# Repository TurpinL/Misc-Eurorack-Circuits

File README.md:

# Misc Eurorack Circuits
Some little circuits I've put together. Mostly heavily referencing if not directly copying other open source circuits. References to be added.

Warning: None of these have been heavily tested (or even lightly, really)

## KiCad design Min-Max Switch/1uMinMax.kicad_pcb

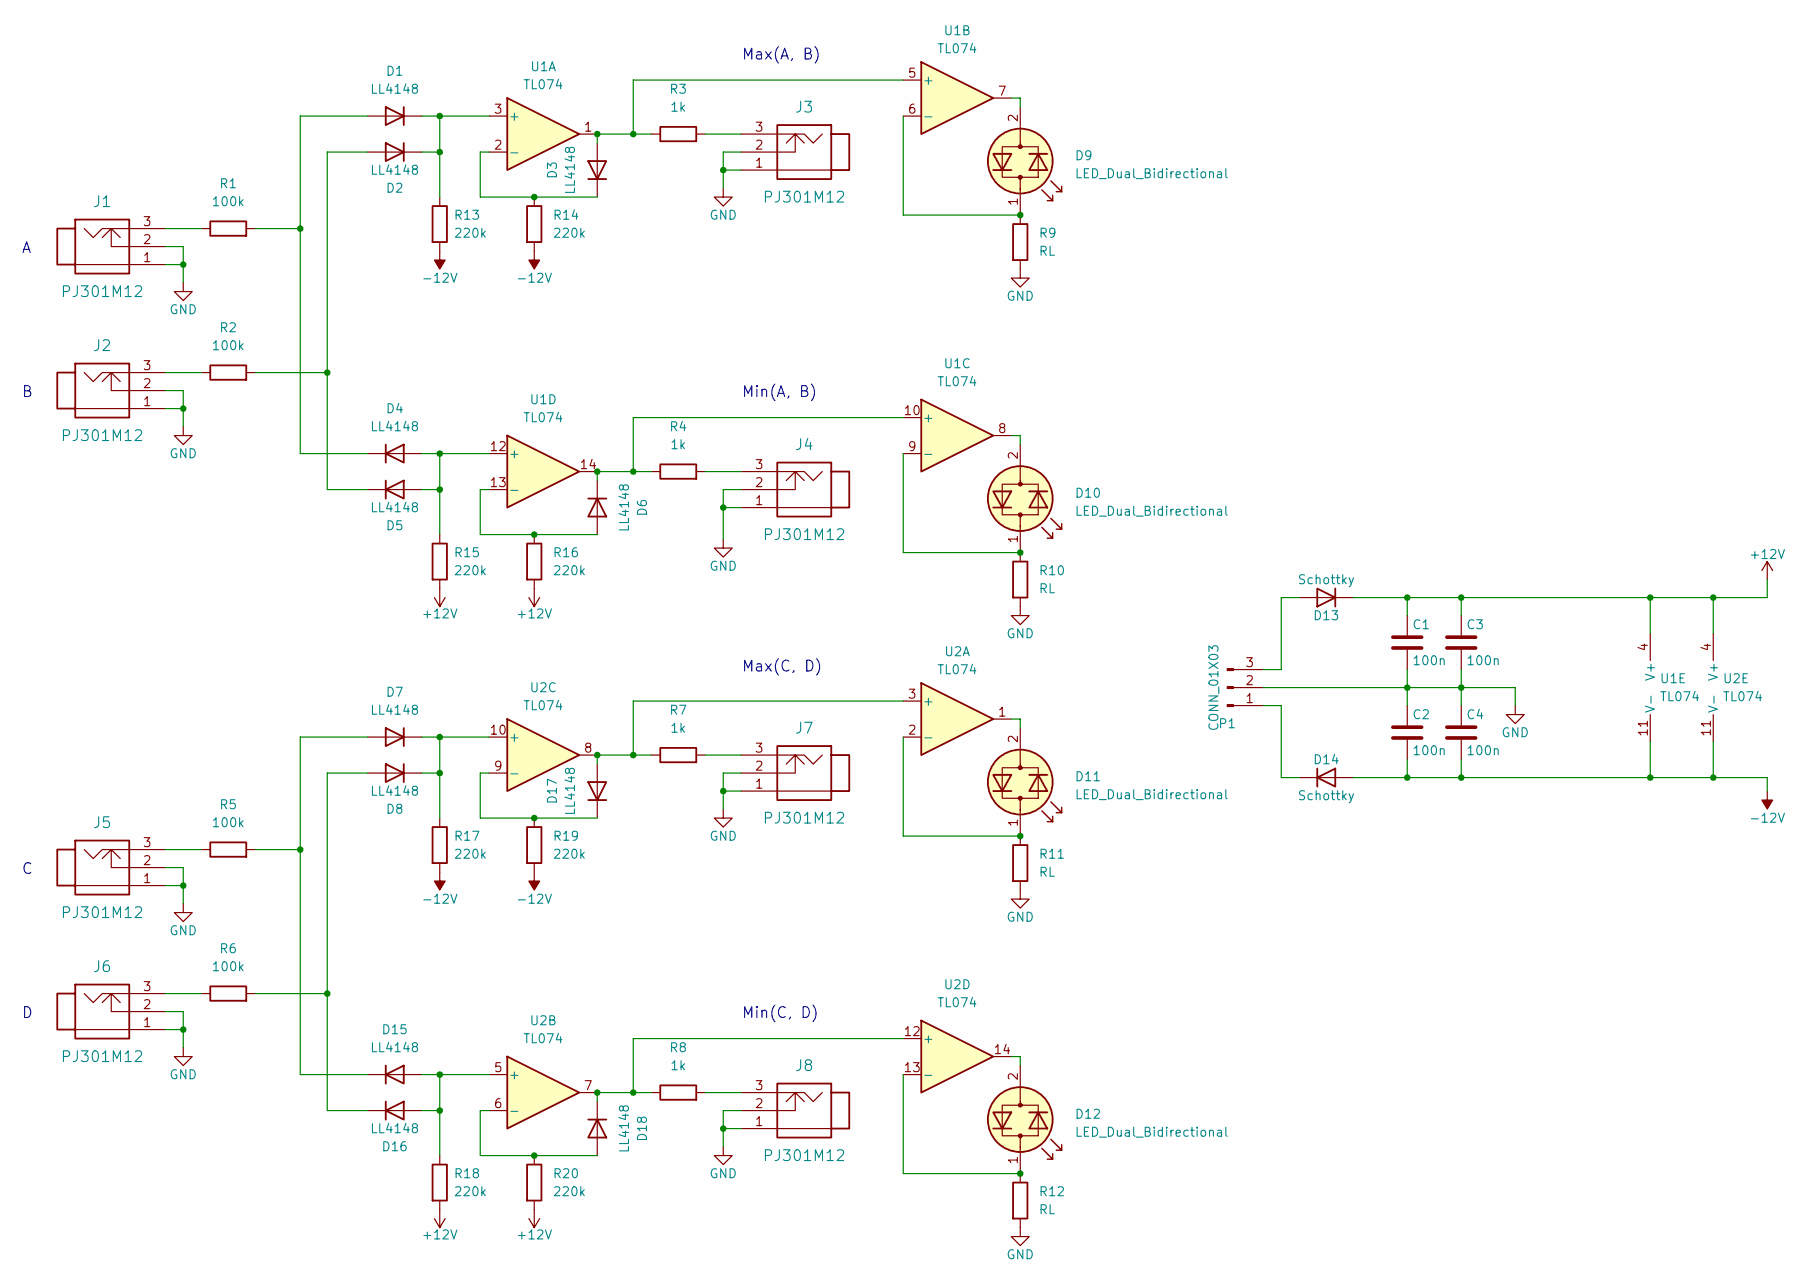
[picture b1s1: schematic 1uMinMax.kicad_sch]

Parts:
C1, C2, C3, C4: 100n; C_0805_2012Metric_Pad1.18x1.45mm_HandSolder
D1, D2, D3, D4, D5, D6, D7, D8, D15, D16, D17, D18: LL4148; D_SOD-323_HandSoldering
D9, D10, D11, D12: LED_Dual_Bidirectional; LED_D3.0mm_Clear
D13, D14: Schottky; D_SOD-323_HandSoldering
J1, J2, J3, J4, J5, J6, J7, J8: PJ301M12; Jack_3.5mm_QingPu_WQP-PJ398SM_Vertical_CircularHoles
P1: CONN_01X03; IDC-Header_2x05_P2.54mm_Vertical
R1, R2, R5, R6: 100k; R_0805_2012Metric_Pad1.20x1.40mm_HandSolder
R3, R4, R7, R8: 1k; R_0805_2012Metric_Pad1.20x1.40mm_HandSolder
R9, R10, R11, R12: RL; R_0805_2012Metric_Pad1.20x1.40mm_HandSolder
R13, R14, R15, R16, R17, R18, R19, R20: 220k; R_0805_2012Metric_Pad1.20x1.40mm_HandSolder
U1, U2: TL074; SOIC-14_3.9x8.7mm_P1.27mm

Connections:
+12V: C1.1, C3.1, D13.1 (K), R15.2, R16.2, R18.2, R20.2, U1.4 (V+), U2.4 (V+)
-12V: C2.2, C4.2, D14.2 (A), R13.2, R14.2, R17.2, R19.2, U1.11 (V-), U2.11 (V-)
GND: C1.2, C2.1, C3.2, C4.1, J1.1, J1.2, J2.1, J2.2, J3.1, J3.2, J4.1, J4.2, J5.1, J5.2, J6.1, J6.2, J7.1, J7.2, J8.1, J8.2, P1.2, R9.2, R10.2, R11.2, R12.2
unnamed: D1.2 (A), D4.1 (K), R1.2
unnamed: D1.1 (K), D2.1 (K), R13.1, U1.3 (+)
unnamed: D2.2 (A), D5.1 (K), R2.2
unnamed: D3.2 (A), R3.1, U1.1, U1.5 (+)
unnamed: D3.1 (K), R14.1, U1.2 (-)
unnamed: D4.2 (A), D5.2 (A), R15.1, U1.12 (+)
unnamed: D6.2 (A), R16.1, U1.13 (-)
unnamed: D6.1 (K), R4.1, U1.10 (+), U1.14
unnamed: D7.1 (K), D8.1 (K), R17.1, U2.10 (+)
unnamed: D9.2 (AK), U1.7
unnamed: D9.1 (KA), R9.1, U1.6 (-)
unnamed: D10.2 (AK), U1.8
unnamed: D10.1 (KA), R10.1, U1.9 (-)
unnamed: D11.2 (AK), U2.1
unnamed: D11.1 (KA), R11.1, U2.2 (-)
unnamed: D12.2 (AK), U2.14
unnamed: D12.1 (KA), R12.1, U2.13 (-)
unnamed: D13.2 (A), P1.3
unnamed: D14.1 (K), P1.1
unnamed: D15.2 (A), D16.2 (A), R18.1, U2.5 (+)
unnamed: D7.2 (A), D15.1 (K), R5.2
unnamed: D8.2 (A), D16.1 (K), R6.2
unnamed: D17.2 (A), R7.1, U2.3 (+), U2.8
unnamed: D17.1 (K), R19.1, U2.9 (-)
unnamed: D18.2 (A), R20.1, U2.6 (-)
unnamed: D18.1 (K), R8.1, U2.7, U2.12 (+)
unnamed: J1.3, R1.1
unnamed: J2.3, R2.1
unnamed: J3.3, R3.2
unnamed: J4.3, R4.2
unnamed: J5.3, R5.1
unnamed: J6.3, R6.1
unnamed: J7.3, R7.2
unnamed: J8.3, R8.2

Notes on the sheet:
Max(C, D)
Min(C, D)
Max(A, B)
Min(A, B)

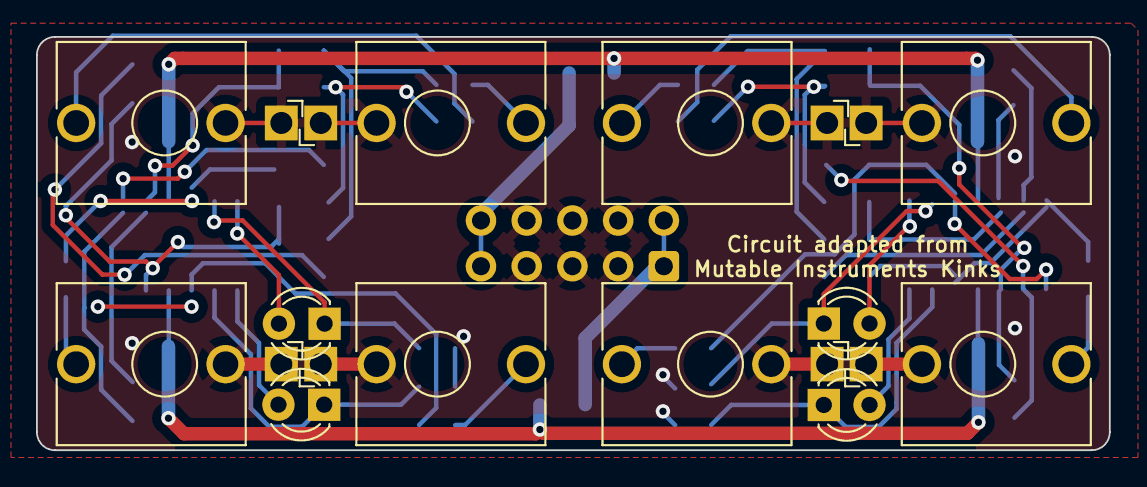
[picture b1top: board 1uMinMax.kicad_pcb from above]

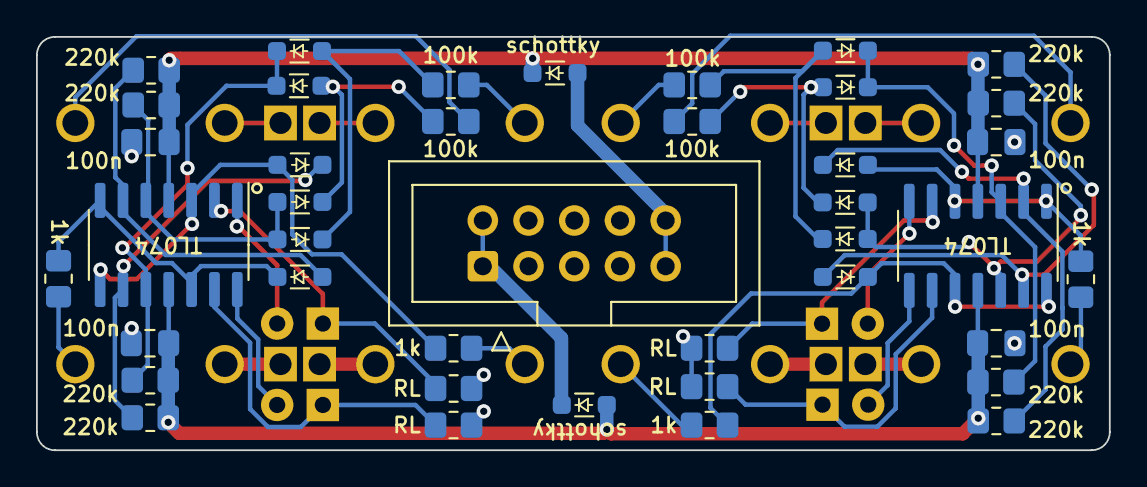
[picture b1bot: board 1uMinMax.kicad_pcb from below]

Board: 2 copper layers, 59.6 x 23.0 mm, 53 parts (41 on the bottom side), 37 nets.

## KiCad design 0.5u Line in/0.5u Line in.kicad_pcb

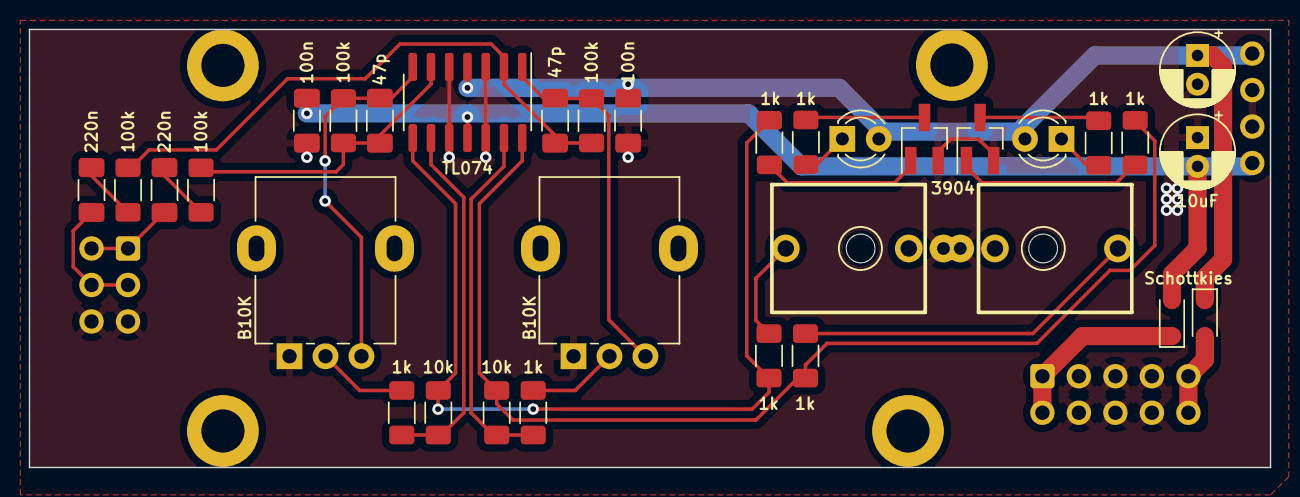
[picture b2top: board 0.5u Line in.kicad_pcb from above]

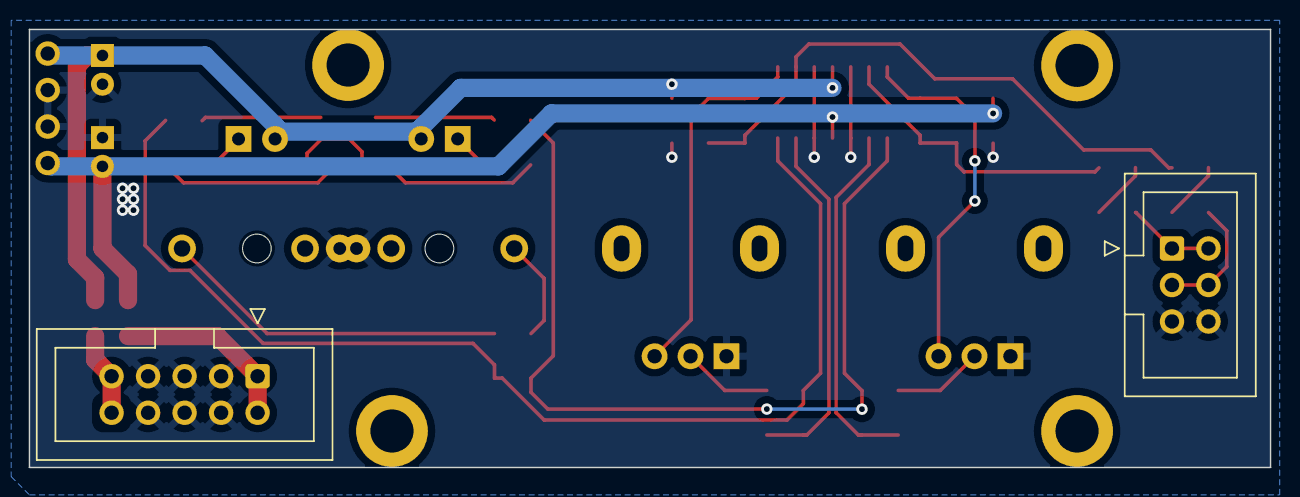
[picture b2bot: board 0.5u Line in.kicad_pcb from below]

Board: 2 copper layers, 86.4 x 30.5 mm, 36 parts (3 on the bottom side), 27 nets.

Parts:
C1, C2: 100n; C_1206_3216Metric_Pad1.33x1.80mm_HandSolder
C3, C4: 10uF; CP_Radial_D5.0mm_P2.00mm
C7, C9: 220n; C_1206_3216Metric_Pad1.33x1.80mm_HandSolder
C8, C10: 47p; C_1206_3216Metric_Pad1.33x1.80mm_HandSolder
D1, D2: D_Schottky; D_SOD-323_HandSoldering
D3, D4: LED; LED_D3.0mm_Clear
J1: Eurorack_Power_10pin_Unshrouded; IDC-Header_2x05_P2.54mm_Vertical
J2: Conn_01x04_Pin; PinHeader_1x04_P2.54mm_Vertical_no_silkscreen
J3: Conn_02x03; IDC-Header_2x03_P2.54mm_Vertical
J4, J5: IN R; EighthInch_PJ398SM_with_hole
Q1, Q2: 3904; SOT-23_Handsoldering
R1, R2, R8, R9: 100k; R_1206_3216Metric_Pad1.30x1.75mm_HandSolder
R3, R5, R6, R7, R10, R12, R13, R14: 1k; R_1206_3216Metric_Pad1.30x1.75mm_HandSolder
R4, R11: 10k; R_1206_3216Metric_Pad1.30x1.75mm_HandSolder
RV1, RV2: B10K; Potentiometer_Alpha_RD901F-40-00D_Single_Vertical
U1: TL074; SOIC-14_3.9x8.7mm_P1.27mm

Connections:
+12v: C1.2, C3.1, D1.1 (K), D3.2 (A), D4.2 (A), J2.1, U1.4 (V+)
-12v: C2.1, C4.2, D2.2 (A), J2.4, U1.11 (V-)
GND: C1.1, C2.2, C3.2, C4.1, J1.3 (GND), J1.4 (GND), J1.5 (GND), J1.6 (GND), J1.7 (GND), J1.8 (GND), J2.2, J2.3, J3.5 (GND), J3.6 (GND), J4.2 (SHEILD), J5.2 (SHEILD), Q1.2 (E), Q2.2 (E), RV1.1, RV2.1, U1.3 (+), U1.5 (+), U1.10 (+), U1.12 (+)
unnamed: C7.1, J3.1 (+12V), J3.2 (+12V)
unnamed: C7.2, R1.1
unnamed: C8.2, R2.2, RV1.3, U1.7
unnamed: C9.1, J3.3 (GND), J3.4 (GND)
unnamed: C9.2, R8.1
unnamed: C10.2, R9.2, RV2.3, U1.1
unnamed: D1.2 (A), J1.1 (+12V), J1.2 (+12V)
unnamed: D2.1 (K), J1.9 (-12V), J1.10 (-12V)
unnamed: D3.1 (K), R7.1
unnamed: D4.1 (K), R14.1
unnamed: J4.1 (SIG), R5.2
unnamed: J5.1 (SIG), R12.2
unnamed: Q1.1 (B), R6.2
unnamed: Q1.3 (C), R7.2
unnamed: Q2.1 (B), R13.2
unnamed: Q2.3 (C), R14.2
unnamed: R3.1, RV1.2
unnamed: R10.1, RV2.2
unnamed: C10.1, R8.2, R9.1, U1.2 (-)
unnamed: C8.1, R1.2, R2.1, U1.6 (-)
unnamed: R3.2, R4.1, U1.9 (-)
unnamed: R10.2, R11.1, U1.13 (-)
Out L: R4.2, R5.1, R6.1, U1.8
Out R: R11.2, R12.1, R13.1, U1.14

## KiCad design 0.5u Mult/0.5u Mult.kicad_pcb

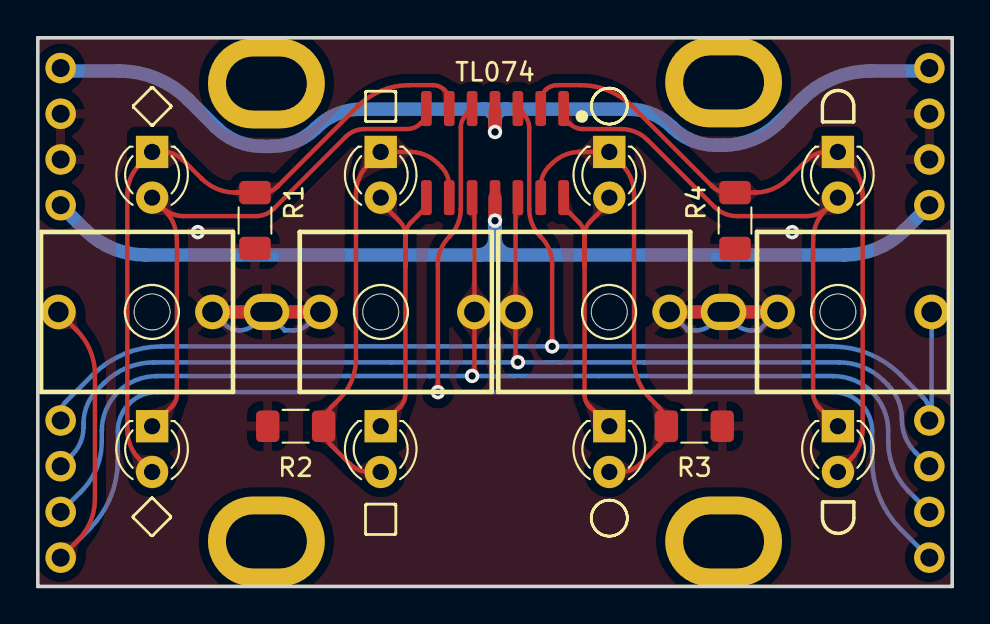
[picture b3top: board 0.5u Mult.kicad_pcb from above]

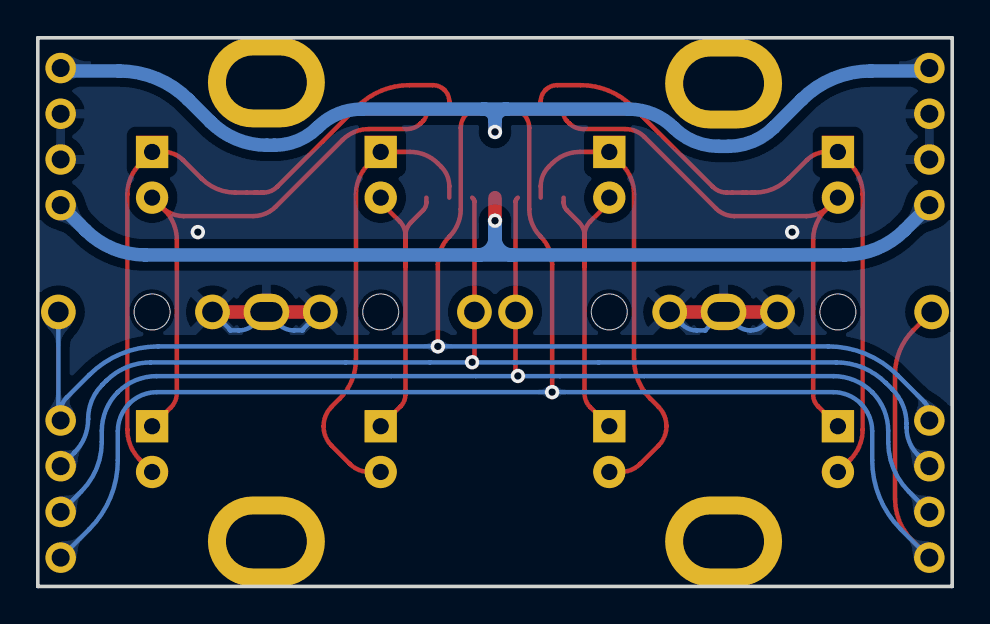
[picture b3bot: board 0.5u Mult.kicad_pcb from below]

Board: 2 copper layers, 50.8 x 30.5 mm, 21 parts (4 on the bottom side), 15 nets.

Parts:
D1, D2, D3, D4, D5, D6, D7, D8: LED; LED_D3.0mm
J1, J2, J3, J4: 3.5mm_Mono_Switched; EighthInch_PJ398SM_with_hole
J5, J6, J7, J8: Conn_01x04_Pin; PinHeader_1x04_P2.54mm_Vertical_no_silkscreen
R1, R2, R3, R4: 1k; R_1206_3216Metric_Pad1.30x1.75mm_HandSolder
TL074: TL074; SOIC-14_3.9x8.7mm_P1.27mm

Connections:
+12v: J5.1, J8.1, TL074.4 (V+)
-12v: J5.4, J8.4, TL074.11 (V-)
GND: J1.2 (SHEILD), J1.3 (SW), J2.3 (SW), J3.2 (SHEILD), J3.3 (SW), J4.3 (SW), J5.2, J5.3, J8.2, J8.3, R1.2, R2.2, R3.2, R4.2
unnamed: D1.2 (A), D2.1 (K), TL074.7
unnamed: D1.1 (K), D2.2 (A), R1.1, TL074.6 (-)
unnamed: D3.2 (A), D4.1 (K), TL074.8
unnamed: D3.1 (K), D4.2 (A), R2.1, TL074.9 (-)
unnamed: D5.2 (A), D6.1 (K), TL074.14
unnamed: D5.1 (K), D6.2 (A), R3.1, TL074.13 (-)
unnamed: D7.2 (A), D8.1 (K), TL074.1
unnamed: D7.1 (K), D8.2 (A), R4.1, TL074.2 (-)
Signal 1: J1.1 (SIG), J6.1, J7.1, TL074.5 (+)
Signal 2: J2.1 (SIG), J6.2, J7.2, TL074.10 (+)
Signal 3: J3.1 (SIG), J6.3, J7.3, TL074.12 (+)
Signal 4: J4.1 (SIG), J6.4, J7.4, TL074.3 (+)

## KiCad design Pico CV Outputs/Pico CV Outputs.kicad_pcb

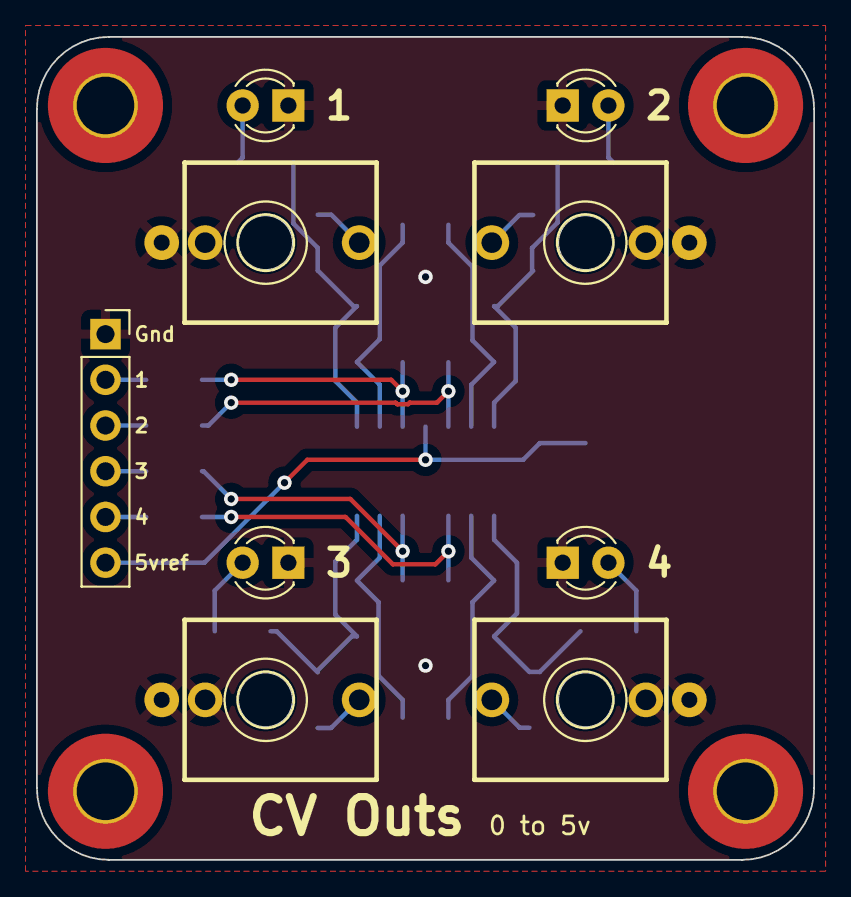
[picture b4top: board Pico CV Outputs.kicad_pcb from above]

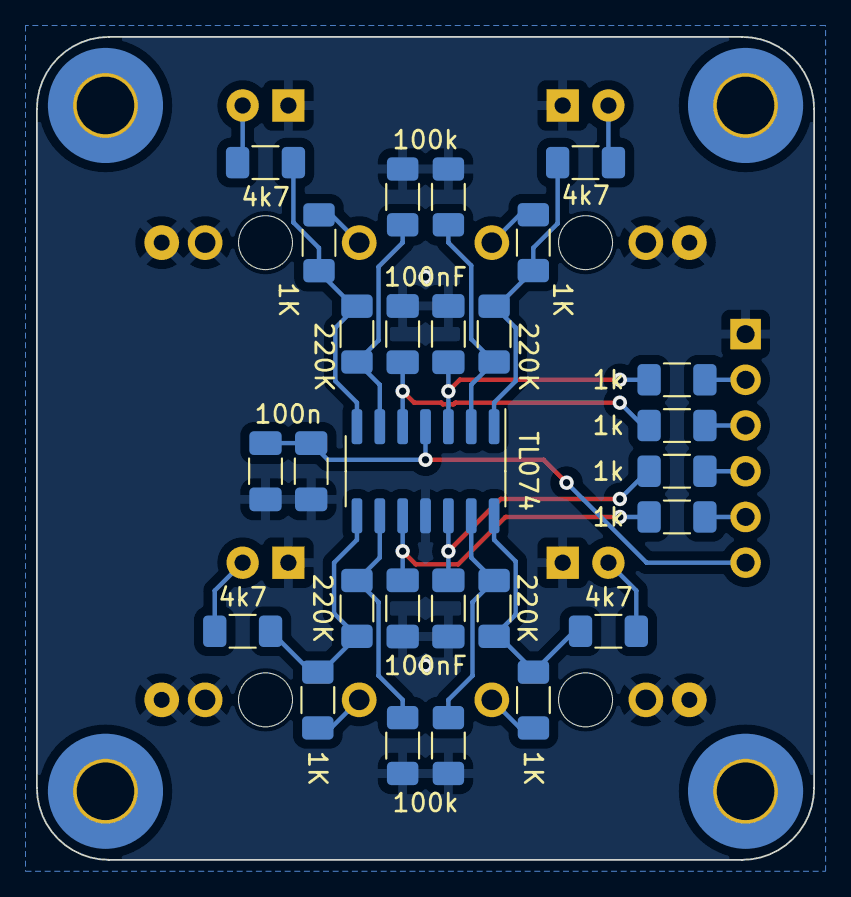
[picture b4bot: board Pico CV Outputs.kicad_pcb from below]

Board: 2 copper layers, 43.2 x 45.7 mm, 36 parts (27 on the bottom side), 26 nets.

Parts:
C1, C4, C5, C6: 100nF; C_1206_3216Metric_Pad1.33x1.80mm_HandSolder
C2, C3: 100n; C_1206_3216Metric_Pad1.33x1.80mm_HandSolder
D1, D2, D3, D4: LED; LED_D3.0mm
J1, J3, J4, J5: 3.5mm_Mono_Switched_SymSmall_0.05; EighthInch_PJ398SM_with_hole
J2: Conn_01x06_Socket; PinSocket_1x06_P2.54mm_Vertical
R1, R6, R11, R16: 1k; R_1206_3216Metric_Pad1.30x1.75mm_HandSolder
R2, R7, R12, R17: 100k; R_1206_3216Metric_Pad1.30x1.75mm_HandSolder
R3, R8, R13, R18: 220K; R_1206_3216Metric_Pad1.30x1.75mm_HandSolder
R4, R10, R15, R20: 1K; R_1206_3216Metric_Pad1.30x1.75mm_HandSolder
R5, R9, R14, R19: 4k7; R_1206_3216Metric_Pad1.30x1.75mm_HandSolder
U1: TL074; SOIC-14_3.9x8.7mm_P1.27mm

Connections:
5vref: C2.1, C3.1, J2.6, U1.4 (V+)
CV 1: J2.2, R1.1
CV 2: J2.3, R6.1
CV 3: J2.4, R11.1
CV 4: J2.5, R16.1
GND: C1.2, C2.2, C3.2, C4.2, C5.2, C6.2, D1.1 (K), D2.1 (K), D3.1 (K), D4.1 (K), J1.2 (SHEILD), J1.3 (SW), J2.1, J3.2 (SHEILD), J3.3 (SW), J4.2 (SHEILD), J4.3 (SW), J5.2 (SHEILD), J5.3 (SW), R2.1, R7.1, R12.1, R17.1, U1.11 (V-)
unnamed: D1.2 (A), R5.2
unnamed: D2.2 (A), R9.2
unnamed: D3.2 (A), R14.2
unnamed: D4.2 (A), R19.2
unnamed: J1.1 (SIG), R4.1
unnamed: J3.1 (SIG), R10.1
unnamed: J4.1 (SIG), R15.1
unnamed: J5.1 (SIG), R20.1
unnamed: R3.1, R4.2, R5.1, U1.1
unnamed: R8.1, R9.1, R10.2, U1.7
unnamed: R13.1, R14.1, R15.2, U1.14
unnamed: R18.1, R19.1, R20.2, U1.8
unnamed: C1.1, R1.2, U1.3 (+)
unnamed: R2.2, R3.2, U1.2 (-)
unnamed: C4.1, R6.2, U1.5 (+)
unnamed: R7.2, R8.2, U1.6 (-)
unnamed: C6.1, R16.2, U1.10 (+)
unnamed: R17.2, R18.2, U1.9 (-)
unnamed: C5.1, R11.2, U1.12 (+)
unnamed: R12.2, R13.2, U1.13 (-)

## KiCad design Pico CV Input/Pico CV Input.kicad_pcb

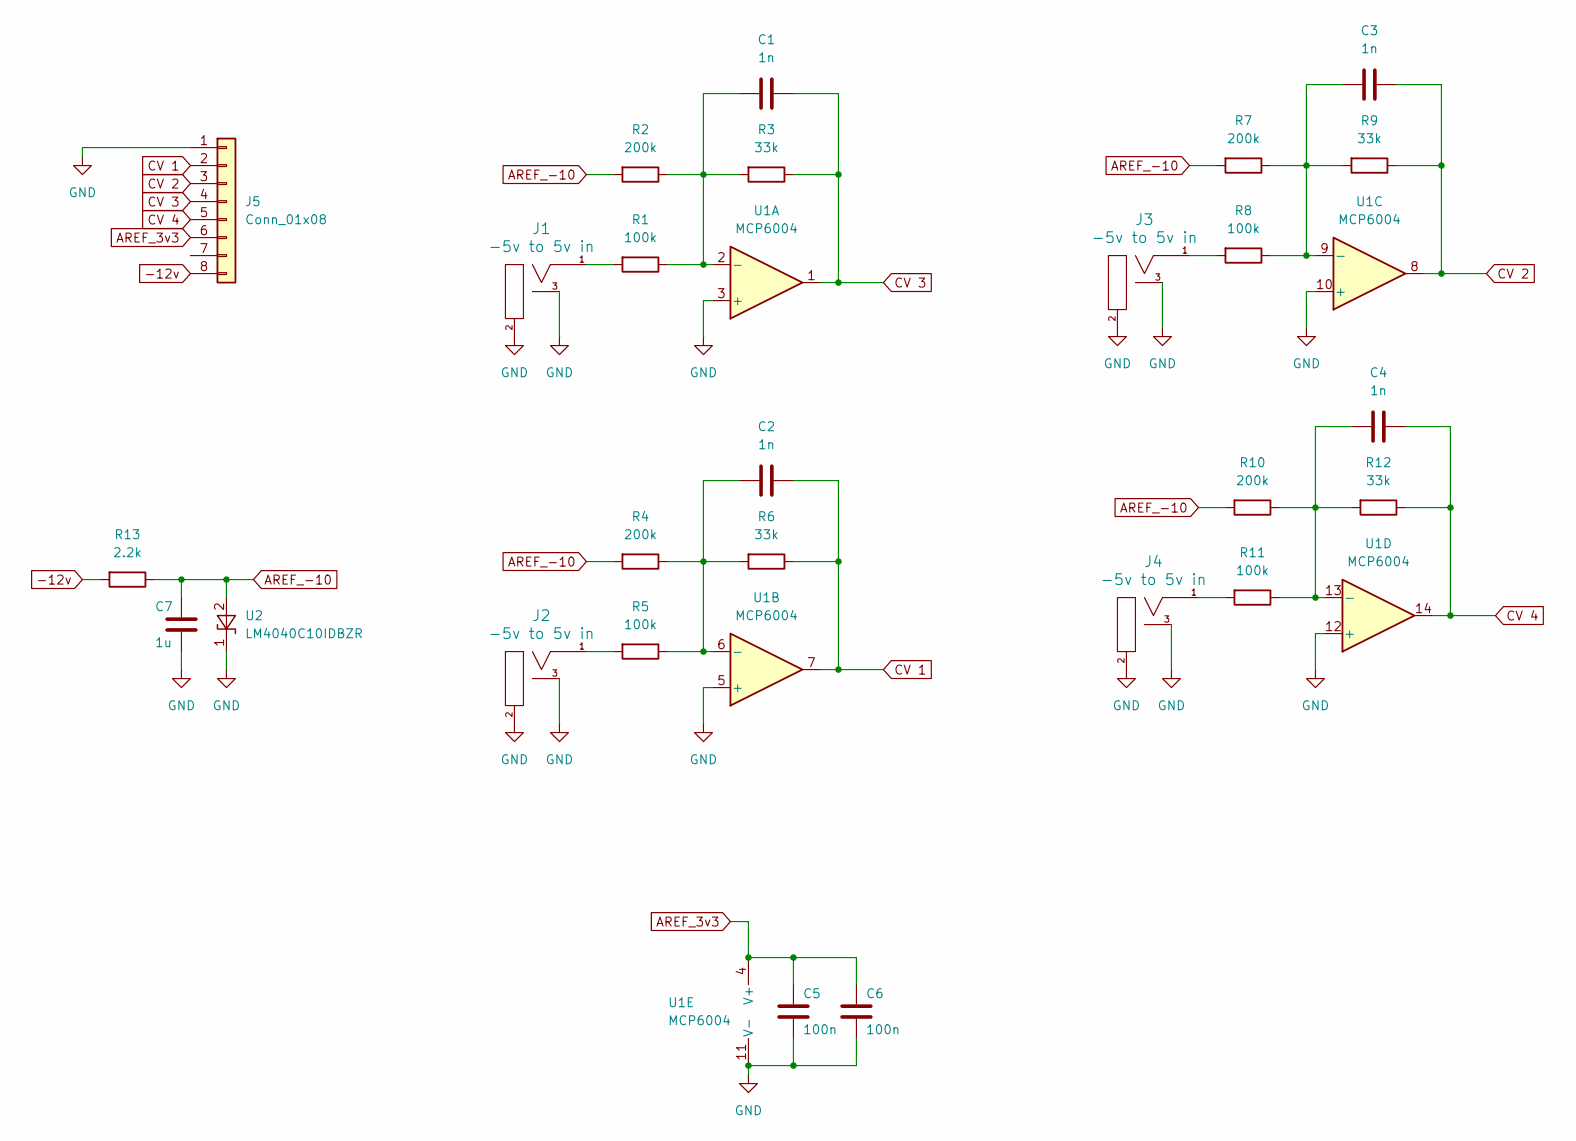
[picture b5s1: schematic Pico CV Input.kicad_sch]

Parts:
C1, C2, C3, C4: 1n; C_1206_3216Metric_Pad1.33x1.80mm_HandSolder
C5, C6: 100n; C_1206_3216Metric_Pad1.33x1.80mm_HandSolder
C7: 1u; C_1206_3216Metric_Pad1.33x1.80mm_HandSolder
J1, J2, J3, J4: -5v to 5v in; EighthInch_PJ398SM_with_hole; Part Number WQP-WQP518MA
J5: Conn_01x08; PinSocket_1x08_P2.54mm_Vertical
R1, R5, R8, R11: 100k; R_1206_3216Metric_Pad1.30x1.75mm_HandSolder
R2, R4, R7, R10: 200k; R_1206_3216Metric_Pad1.30x1.75mm_HandSolder
R3, R6, R9, R12: 33k; R_1206_3216Metric_Pad1.30x1.75mm_HandSolder
R13: 2.2k; R_1206_3216Metric_Pad1.30x1.75mm_HandSolder
U1: MCP6004; SOIC-14_3.9x8.7mm_P1.27mm
U2: LM4040C10IDBZR; SOT-23-3

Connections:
-12v: J5.8, R13.2
AREF_3v3: C5.1, C6.1, J5.6, U1.4 (V+)
AREF_-10: C7.1, R2.2, R4.2, R7.2, R10.2, R13.1, U2.2 (A)
CV 1: C2.2, J5.2, R6.1, U1.7
CV 2: C3.2, J5.3, R9.1, U1.8
CV 3: C1.2, J5.4, R3.1, U1.1
CV 4: C4.2, J5.5, R12.1, U1.14
GND: C5.2, C6.2, C7.2, J1.2 (SHEILD), J1.3 (SW), J2.2 (SHEILD), J2.3 (SW), J3.2 (SHEILD), J3.3 (SW), J4.2 (SHEILD), J4.3 (SW), J5.1, U1.3 (+), U1.5 (+), U1.10 (+), U1.11 (V-), U1.12 (+), U2.1 (K)
unnamed: J1.1 (SIG), R1.2
unnamed: J2.1 (SIG), R5.2
unnamed: J3.1 (SIG), R8.2
unnamed: J4.1 (SIG), R11.2
unnamed: C1.1, R1.1, R2.1, R3.2, U1.2 (-)
unnamed: C2.1, R4.1, R5.1, R6.2, U1.6 (-)
unnamed: C3.1, R7.1, R8.1, R9.2, U1.9 (-)
unnamed: C4.1, R10.1, R11.1, R12.2, U1.13 (-)

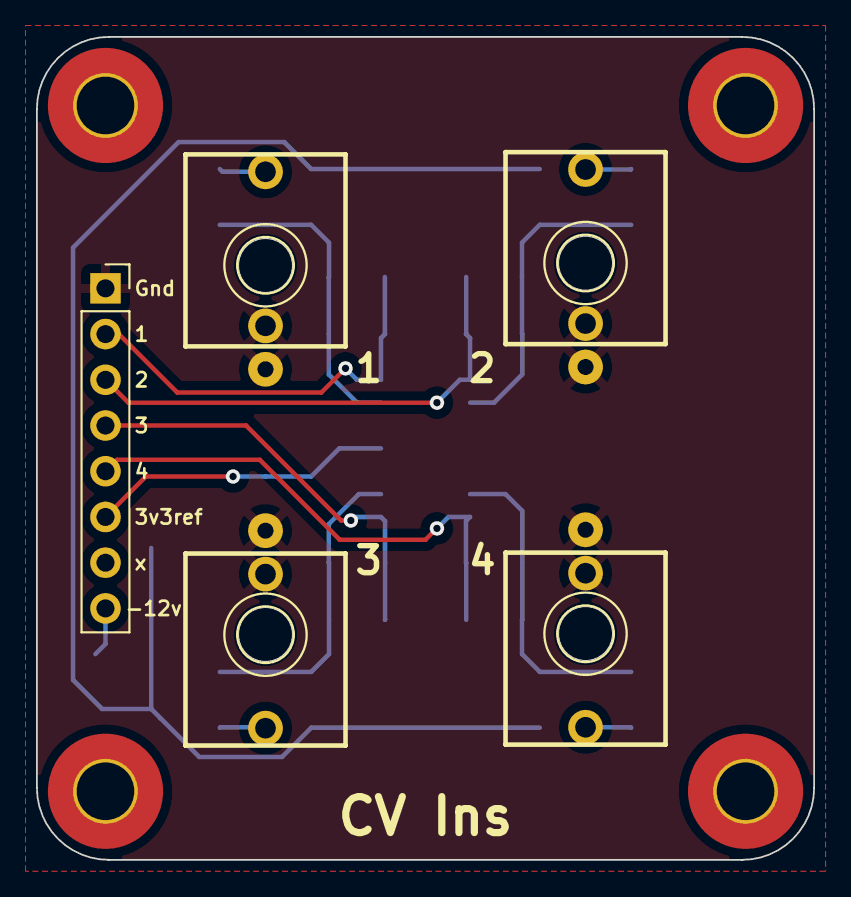
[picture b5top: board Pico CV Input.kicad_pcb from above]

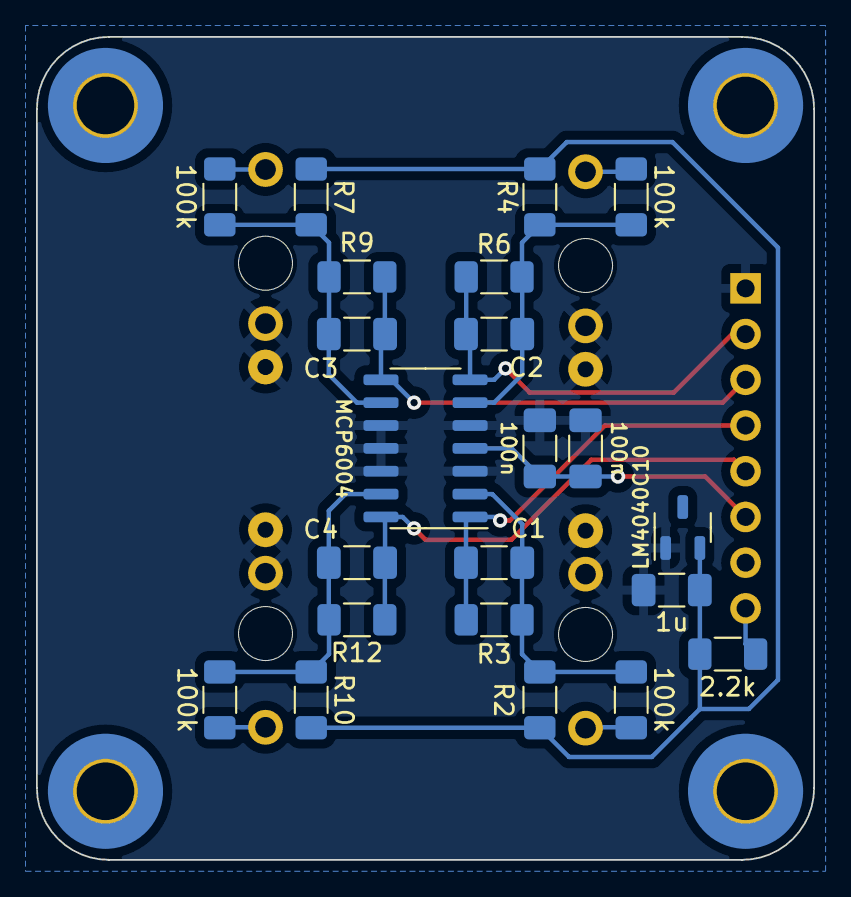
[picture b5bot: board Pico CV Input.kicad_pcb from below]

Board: 2 copper layers, 43.2 x 45.7 mm, 27 parts (22 on the bottom side), 16 nets.

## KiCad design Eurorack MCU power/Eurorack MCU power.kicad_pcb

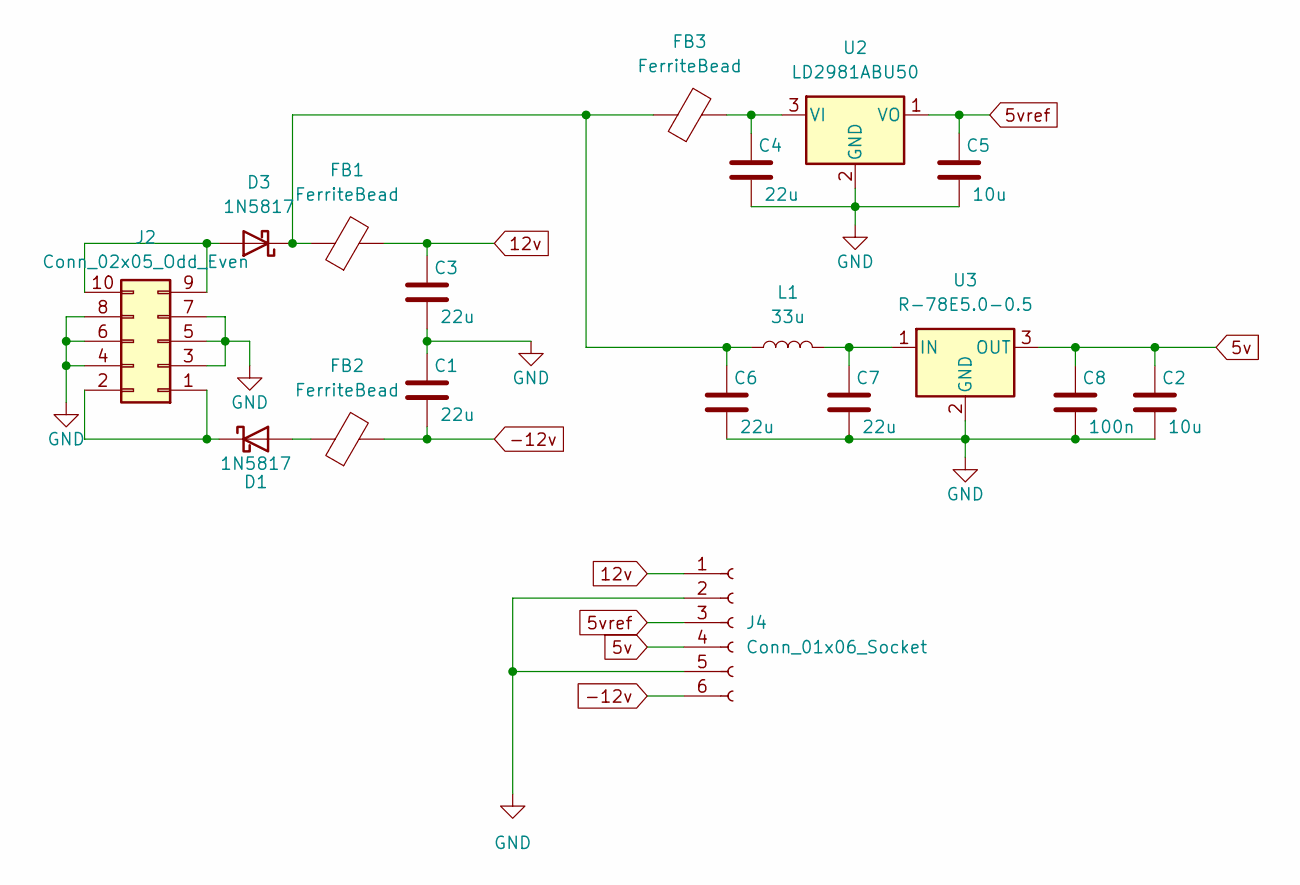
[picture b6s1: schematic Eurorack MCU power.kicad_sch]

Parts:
C1, C3, C4, C6, C7: 22u; C_1206_3216Metric_Pad1.33x1.80mm_HandSolder
C2, C5: 10u; C_1206_3216Metric_Pad1.33x1.80mm_HandSolder
C8: 100n; C_1206_3216Metric_Pad1.33x1.80mm_HandSolder
D1, D3: 1N5817; D_SOD-323_HandSoldering
FB1, FB2, FB3: FerriteBead; L_1206_3216Metric_Pad1.42x1.75mm_HandSolder
J2: Conn_02x05_Odd_Even; IDC-Header_2x05_P2.54mm_Vertical
J4: Conn_01x06_Socket; PinSocket_1x06_P2.54mm_Vertical
L1: 33u; L_0805_2012Metric_Pad1.15x1.40mm_HandSolder
U2: LD2981ABU50; SOT-89-3
U3: R-78E5.0-0.5; Converter_DCDC_RECOM_R-78E-0.5_THT

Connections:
5v: C2.2, C8.2, J4.4, U3.3 (OUT)
5vref: C5.2, J4.3, U2.1 (VO)
12v: C3.2, FB1.2, J4.1
-12v: C1.1, FB2.2, J4.6
GND: C1.2, C2.1, C3.1, C4.1, C5.1, C6.1, C7.1, C8.1, J2.3, J2.4, J2.5, J2.6, J2.7, J2.8, J4.2, J4.5, U2.2 (GND), U3.2 (GND)
unnamed: D1.2 (A), FB2.1
unnamed: D1.1 (K), J2.1, J2.2
unnamed: D3.2 (A), J2.9, J2.10
unnamed: C6.2, D3.1 (K), FB1.1, FB3.1, L1.1
unnamed: C4.2, FB3.2, U2.3 (VI)
unnamed: C7.2, L1.2, U3.1 (IN)

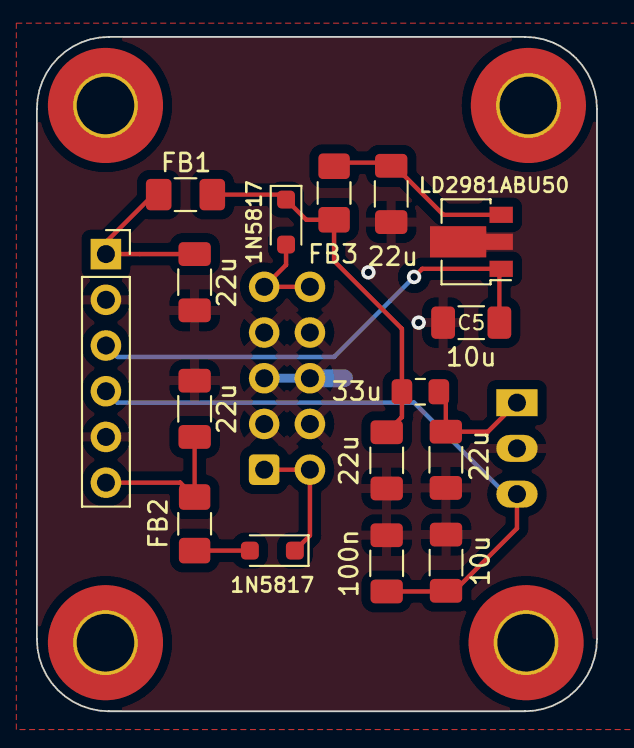
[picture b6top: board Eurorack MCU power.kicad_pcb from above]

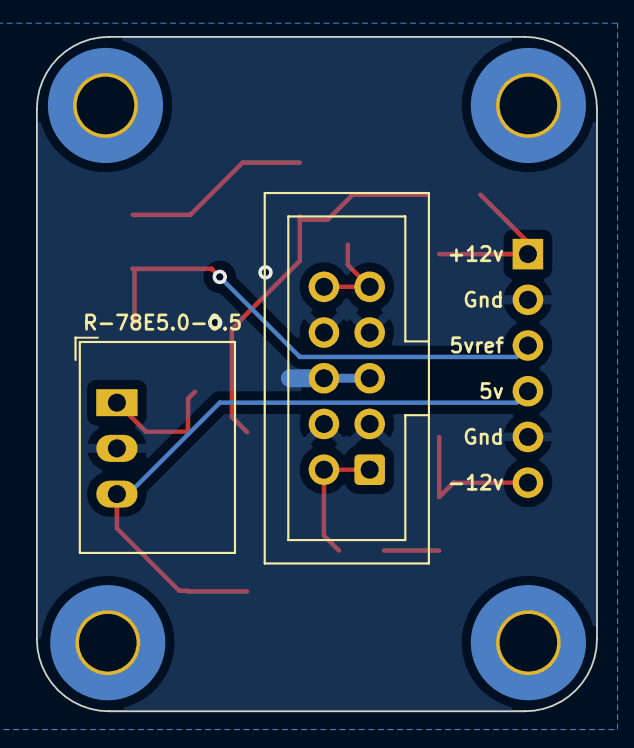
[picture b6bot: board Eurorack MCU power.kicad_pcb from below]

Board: 2 copper layers, 31.1 x 37.5 mm, 18 parts (2 on the bottom side), 11 nets.

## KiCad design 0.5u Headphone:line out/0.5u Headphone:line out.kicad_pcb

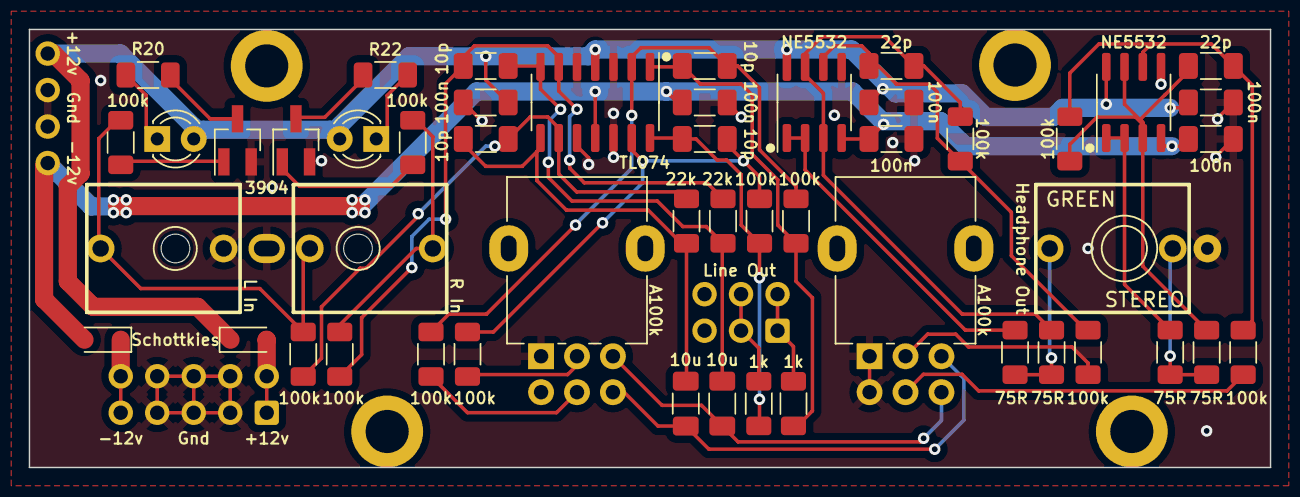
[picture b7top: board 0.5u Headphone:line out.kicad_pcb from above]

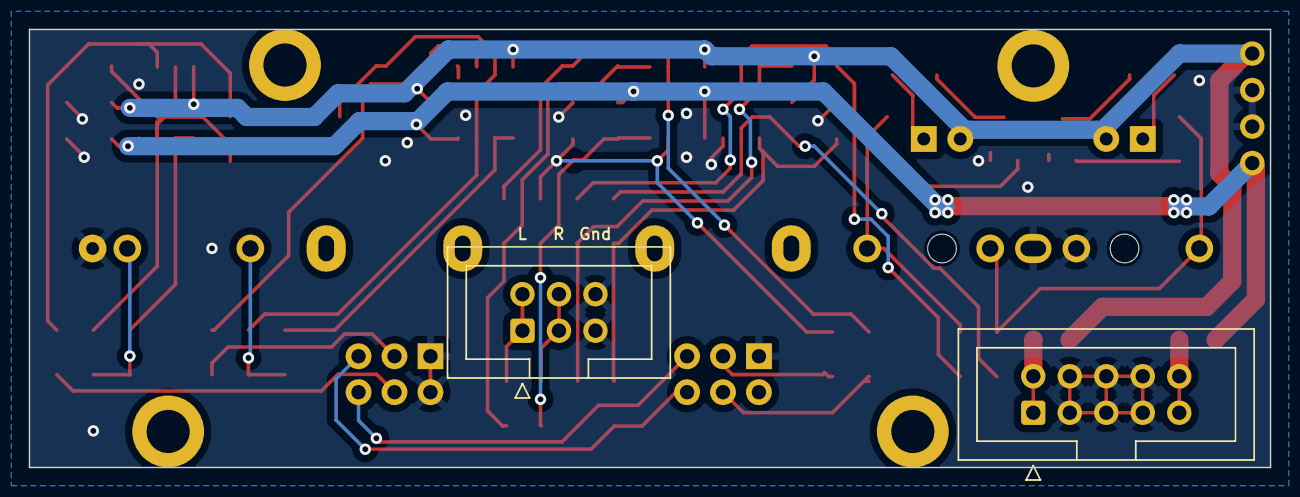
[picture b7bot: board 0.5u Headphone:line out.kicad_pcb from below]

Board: 2 copper layers, 86.4 x 30.5 mm, 53 parts (3 on the bottom side), 37 nets.

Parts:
C1, C2, C3, C4: 10p; C_1206_3216Metric_Pad1.33x1.80mm_HandSolder
C5, C6: 22p; C_1206_3216Metric_Pad1.33x1.80mm_HandSolder
C9, C10, C11, C12, C13, C14: 100n; C_1206_3216Metric_Pad1.33x1.80mm_HandSolder
C15, C16: 10u; C_1206_3216Metric_Pad1.33x1.80mm_HandSolder
D1, D2: LED; LED_D3.0mm_Clear
D3, D4: D_Schottky; D_SOD-323_HandSoldering
J1: IN L; EighthInch_PJ398SM_with_hole
J2: IN R; EighthInch_PJ398SM_with_hole
J3: Eurorack_Power_10pin_Unshrouded; IDC-Header_2x05_P2.54mm_Vertical
J4: 3.5mm_Stereo; EighthInch_Stereo_PJ366ST
J5: Conn_02x03; IDC-Header_2x03_P2.54mm_Vertical
J6: Conn_01x04_Pin; PinHeader_1x04_P2.54mm_Vertical_no_silkscreen
Q1, Q2: 3904; SOT-23_Handsoldering
R1, R3, R4, R6, R8, R9, R11, R12, R14, R15, R19, R21: 100k; R_1206_3216Metric_Pad1.30x1.75mm_HandSolder
R2, R7: 22k; R_1206_3216Metric_Pad1.30x1.75mm_HandSolder
R5, R10, R20, R22: 1k; R_1206_3216Metric_Pad1.30x1.75mm_HandSolder
R13, R16, R23, R24: 75R; R_1206_3216Metric_Pad1.30x1.75mm_HandSolder
RV1, RV2: R_Potentiometer_Dual 100k; Potentiometer_Alpha_RD902F-40-00D_Dual_Vertical
U1: TL074; SOIC-14_3.9x8.7mm_P1.27mm
U3, U4: NE5532; SOIC-8_3.9x4.9mm_P1.27mm

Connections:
+12v: C9.2, C11.2, C13.2, D1.2 (A), D2.2 (A), D3.1 (K), J6.1, U1.4 (V+), U3.8 (V+), U4.8 (V+)
-12v: C10.1, C12.1, C14.1, D4.2 (A), J6.4, U1.11 (V-), U3.4 (V-), U4.4 (V-)
GND: C9.1, C10.2, C11.1, C12.2, C13.1, C14.2, J1.2 (SHEILD), J1.3 (SW), J3.3 (GND), J3.4 (GND), J3.5 (GND), J3.6 (GND), J3.7 (GND), J3.8 (GND), J4.2 (SHEILD), J5.5 (GND), J5.6 (GND), J6.2, J6.3, Q1.2 (E), Q2.2 (E), RV1.1, RV1.4, RV2.1, U1.3 (+), U1.5 (+), U1.10 (+), U1.12 (+), U3.5 (+), U4.5 (+)
In L: J1.1 (SIG), J2.3 (SW), R1.1, R19.1
In R: J2.1 (SIG), R6.1, R21.1
Intermediate L: C15.2, RV1.3, RV2.6
Intermediate R: C16.2, RV1.6, RV2.3
unnamed: C1.2, C15.1, R2.2, U1.8
unnamed: C2.2, R4.2, R5.1, U1.1
unnamed: C4.2, R9.2, R10.1, U1.14
unnamed: C3.2, C16.1, R7.2, U1.7
unnamed: D1.1 (K), R20.1
unnamed: D2.1 (K), R22.1
unnamed: D3.2 (A), J3.1 (+12V), J3.2 (+12V)
unnamed: D4.1 (K), J3.9 (-12V), J3.10 (-12V)
unnamed: J4.1 (SIG), R13.2, R23.2
unnamed: J4.3 (SW), R16.2, R24.2
unnamed: J5.1 (+12V), J5.2 (+12V), R5.2
unnamed: J5.3 (GND), J5.4 (GND), R10.2
unnamed: Q1.1 (B), R19.2
unnamed: Q1.3 (C), R20.2
unnamed: Q2.1 (B), R21.2
unnamed: Q2.3 (C), R22.2
unnamed: R3.1, RV2.5
unnamed: R8.1, RV2.2
unnamed: R11.1, RV1.2
unnamed: R14.1, RV1.5
unnamed: C2.1, R3.2, R4.1, U1.2 (-)
unnamed: C3.1, R6.2, R7.1, U1.6 (-)
unnamed: C1.1, R1.2, R2.1, U1.9 (-)
unnamed: C4.1, R8.2, R9.1, U1.13 (-)
unnamed: C5.2, R12.2, R13.1, U3.3 (+), U3.7
unnamed: R23.1, U3.1, U3.2 (-)
unnamed: C5.1, R11.2, R12.1, U3.6 (-)
unnamed: C6.2, R15.2, R16.1, U4.3 (+), U4.7
unnamed: R24.1, U4.1, U4.2 (-)
unnamed: C6.1, R14.2, R15.1, U4.6 (-)

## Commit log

2023-11-10 Schematics
2023-11-10 Some slight context
2024-06-11 Min Max Switch
2024-06-12 Updated sub-dom switch circuit. It now clones a section of the Mutable Instruments Kinks circuit
2024-06-17 Updated diode silkscreen
